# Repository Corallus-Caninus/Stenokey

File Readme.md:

# Stenokey - pico
This is a mod of Mike ady's Stenokey I have only 
tried to improve on their work and make it more accessible/affordable.

This fork implements a Pico and removes all components on the PCB except the switches. 
Configuration is done in software. 

The firmware was uploaded with Arduino using the pico board found in the board manager.
the default driver is TX Bolt and can be set in Plover's Configuration. The baud rate is 115200.
All drivers should work except NKRO keyboard since it's implemented as a teensy 
builtin protocol at this time.

---

Stenographic keyboard

Stenokey is an open source do it yourself stenographic keyboard project.  It is aimed 
at makers with some electronics experience (soldering) and who own a 3D printer 
or who have a friend with a 3D printer.

Stenokey connects to any desktop or laptop PC that has a USB port.  It is meant 
to work with the Open Steno Project's Plover software, which runs on Linux, Mac and 
Windows.

This project consists of four main parts:

- The OpenSCAD source code for all of the 3D printed plastic parts is in the main 
directory.  Printer ready .STL files for the key tops are in the Key\_Print\_Files 
directory.  The .STL files for the case are in the Case\_Print\_Files directory.  

- The bill of materials (BOM) for populating the circuit board is in the main 
directory.  The PCB design files are in the PCB directory.

- The Arduino based firmware is in the Firmware directory.

- Documentation for the project, including build instructions, programming and testing 
instructions and a user manual are all in the Documentation Directory.

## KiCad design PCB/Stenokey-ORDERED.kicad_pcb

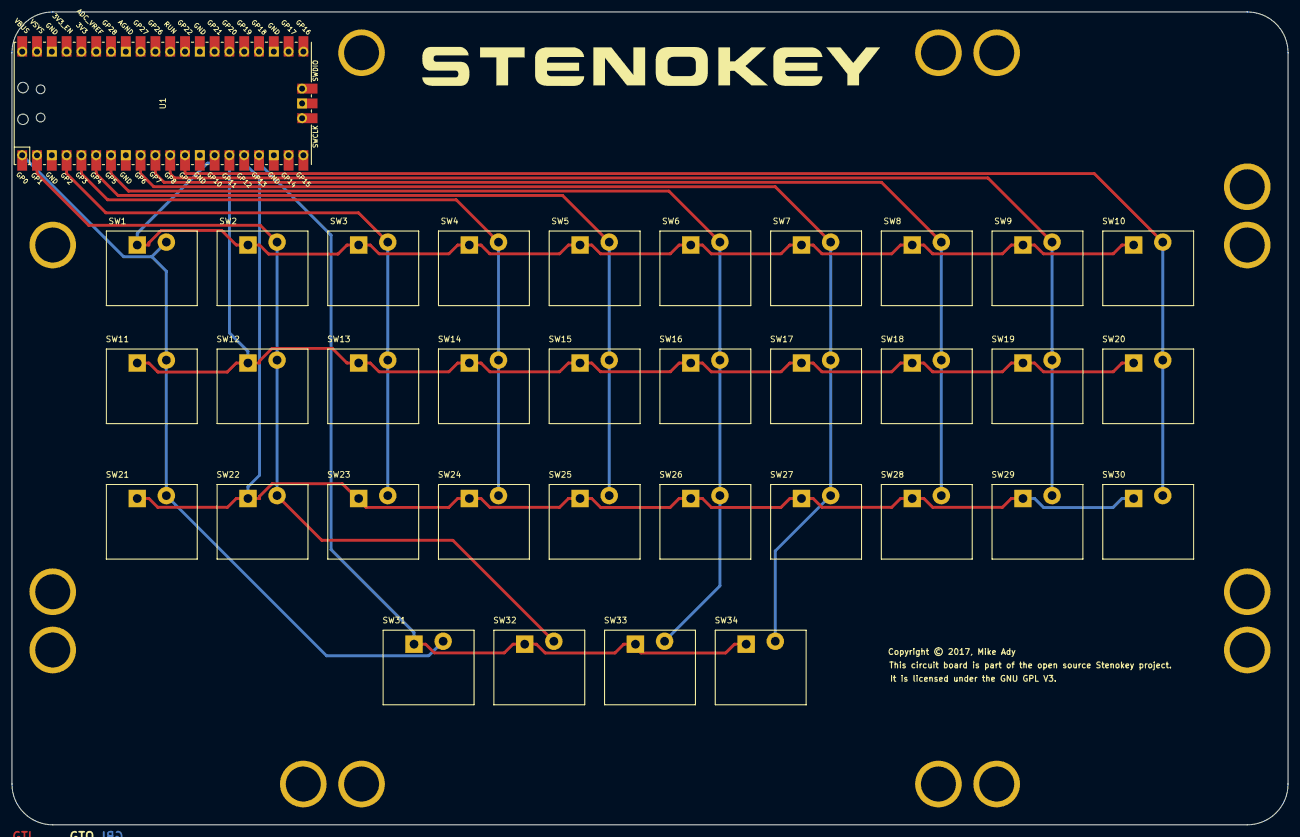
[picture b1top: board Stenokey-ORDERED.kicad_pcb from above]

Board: 2 copper layers, 219.0 x 139.5 mm, 51 parts (0 on the bottom side), 14 nets.

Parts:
SW1: KEY_R1C1; SW_Matias_Quiet
SW2: KEY_R1C2; SW_Matias_Quiet
SW3: KEY_R1C3; SW_Matias_Quiet
SW4: KEY_R1C4; SW_Matias_Quiet
SW5: KEY_R1C5; SW_Matias_Quiet
SW6: KEY_R1C6; SW_Matias_Quiet
SW7: KEY_R1C7; SW_Matias_Quiet
SW8: KEY_R1C8; SW_Matias_Quiet
SW9: KEY_R1C9; SW_Matias_Quiet
SW10: KEY_R1C10; SW_Matias_Quiet
SW11: KEY_R2C1; SW_Matias_Quiet
SW12: KEY_R2C2; SW_Matias_Quiet
SW13: KEY_R2C3; SW_Matias_Quiet
SW14: KEY_R2C4; SW_Matias_Quiet
SW15: KEY_R2C5; SW_Matias_Quiet
SW16: KEY_R2C6; SW_Matias_Quiet
SW17: KEY_R2C7; SW_Matias_Quiet
SW18: KEY_R2C8; SW_Matias_Quiet
SW19: KEY_R2C9; SW_Matias_Quiet
SW20: KEY_R2C10; SW_Matias_Quiet
SW21: KEY_R3C1; SW_Matias_Quiet
SW22: KEY_R3C2; SW_Matias_Quiet
SW23: KEY_R3C3; SW_Matias_Quiet
SW24: KEY_R3C4; SW_Matias_Quiet
SW25: KEY_R3C5; SW_Matias_Quiet
SW26: KEY_R3C6; SW_Matias_Quiet
SW27: KEY_R3C7; SW_Matias_Quiet
SW28: KEY_R3C8; SW_Matias_Quiet
SW29: KEY_R3C9; SW_Matias_Quiet
SW30: KEY_R3C10; SW_Matias_Quiet
SW31: KEY_R4C1; SW_Matias_Quiet
SW32: KEY_R4C2; SW_Matias_Quiet
SW33: KEY_R4C6; SW_Matias_Quiet
SW34: KEY_R4C7; SW_Matias_Quiet
U1: Pico; RPi_Pico_SMD_TH
Z2, Z3, Z4, Z5, Z6, Z7, Z8, Z9, Z10, Z11, Z12, Z13, Z14, Z15: Hole; HOLE_600800
Z17: Copyright
Z18: Logo; StenoKeyLogo

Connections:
/COL0: SW1.2, SW11.2, SW21.2, SW31.2, U1.1
/COL1: SW2.2, SW12.2, SW22.2, SW32.2, U1.2
/COL2: SW3.2, SW13.2, SW23.2, U1.4
/COL3: SW4.2, SW14.2, SW24.2, U1.5
/COL4: SW5.2, SW15.2, SW25.2, U1.6
/COL5: SW6.2, SW16.2, SW26.2, SW33.2, U1.7
/COL6: SW7.2, SW17.2, SW27.2, SW34.2, U1.9
/COL7: SW8.2, SW18.2, SW28.2, U1.10
/COL8: SW9.2, SW19.2, SW29.2, U1.11
/COL9: SW10.2, SW20.2, SW30.2, U1.12
/ROW0: SW1.1, SW2.1, SW3.1, SW4.1, SW5.1, SW6.1, SW7.1, SW8.1, SW9.1, SW10.1, U1.14
/ROW1: SW11.1, SW12.1, SW13.1, SW14.1, SW15.1, SW16.1, SW17.1, SW18.1, SW19.1, SW20.1, U1.15
/ROW2: SW21.1, SW22.1, SW23.1, SW24.1, SW25.1, SW26.1, SW27.1, SW28.1, SW29.1, SW30.1, U1.16
/ROW3: SW31.1, SW32.1, SW33.1, SW34.1, U1.17

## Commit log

2021-06-15 initial_commit pico
2021-06-15 implement PULL_DOWN internal pico resistor
2021-06-16 begin bounce detection algorithm (unreadable)
2021-06-16 synchronize chord press and release in bounce trigger
2021-06-16 inline column read and row read
2021-06-25 initial State Machine and DMA prototype

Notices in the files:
PCB/Stenokey-ORDERED.kicad_pcb:
Copyright © 2017, Mike Ady
The Stenokey circuit board is open source.  It is licensed under the GNU GPL V3.0.
parts and their libraries:
It is licensed under the GNU GPL V3.
